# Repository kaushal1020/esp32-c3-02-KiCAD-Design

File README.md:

# ESP32-C3-02 KiCad Design

A custom **ESP32-C3-02 Development Board** designed from scratch using **KiCad**. This repository contains the complete hardware design, including schematic, PCB layout, and supporting files for manufacturing and development.

---

## 📖 Project Overview

This project demonstrates the complete design of an ESP32-C3-02 based development board. The board is intended for embedded systems, IoT applications, and custom hardware development.

The design was created entirely in KiCad, following standard PCB design practices.

---

## ✨ Features

- ESP32-C3-02 Wi-Fi + Bluetooth MCU
- USB programming interface
- Power regulation circuit
- Reset and Boot buttons
- GPIO breakout
- Status LEDs
- Compact PCB layout
- Designed completely in KiCad

---

## 📂 Repository Contents

- Schematic (.kicad_sch)
- PCB Layout (.kicad_pcb)
- KiCad Project Files
- Symbol Libraries
- Footprint Libraries
- Manufacturing Files (Gerbers)
- Bill of Materials (BOM)

---

## 🛠 Software Used

- KiCad 9
- ESP32-C3-02

## 🚀 Applications

- IoT Devices
- Embedded Systems
- Wireless Sensor Networks
- Industrial Monitoring
- Robotics

---

## 📋 Future Improvements

- Add USB-C interface
- Battery charging circuit
- On-board sensors
- Power optimization
- Improved GPIO labeling

---

## 📄 License

This project is intended for educational and learning purposes.

---

## 👨‍💻 Author

**Kaushal Kumar**

GitHub: https://github.com/kaushal1020

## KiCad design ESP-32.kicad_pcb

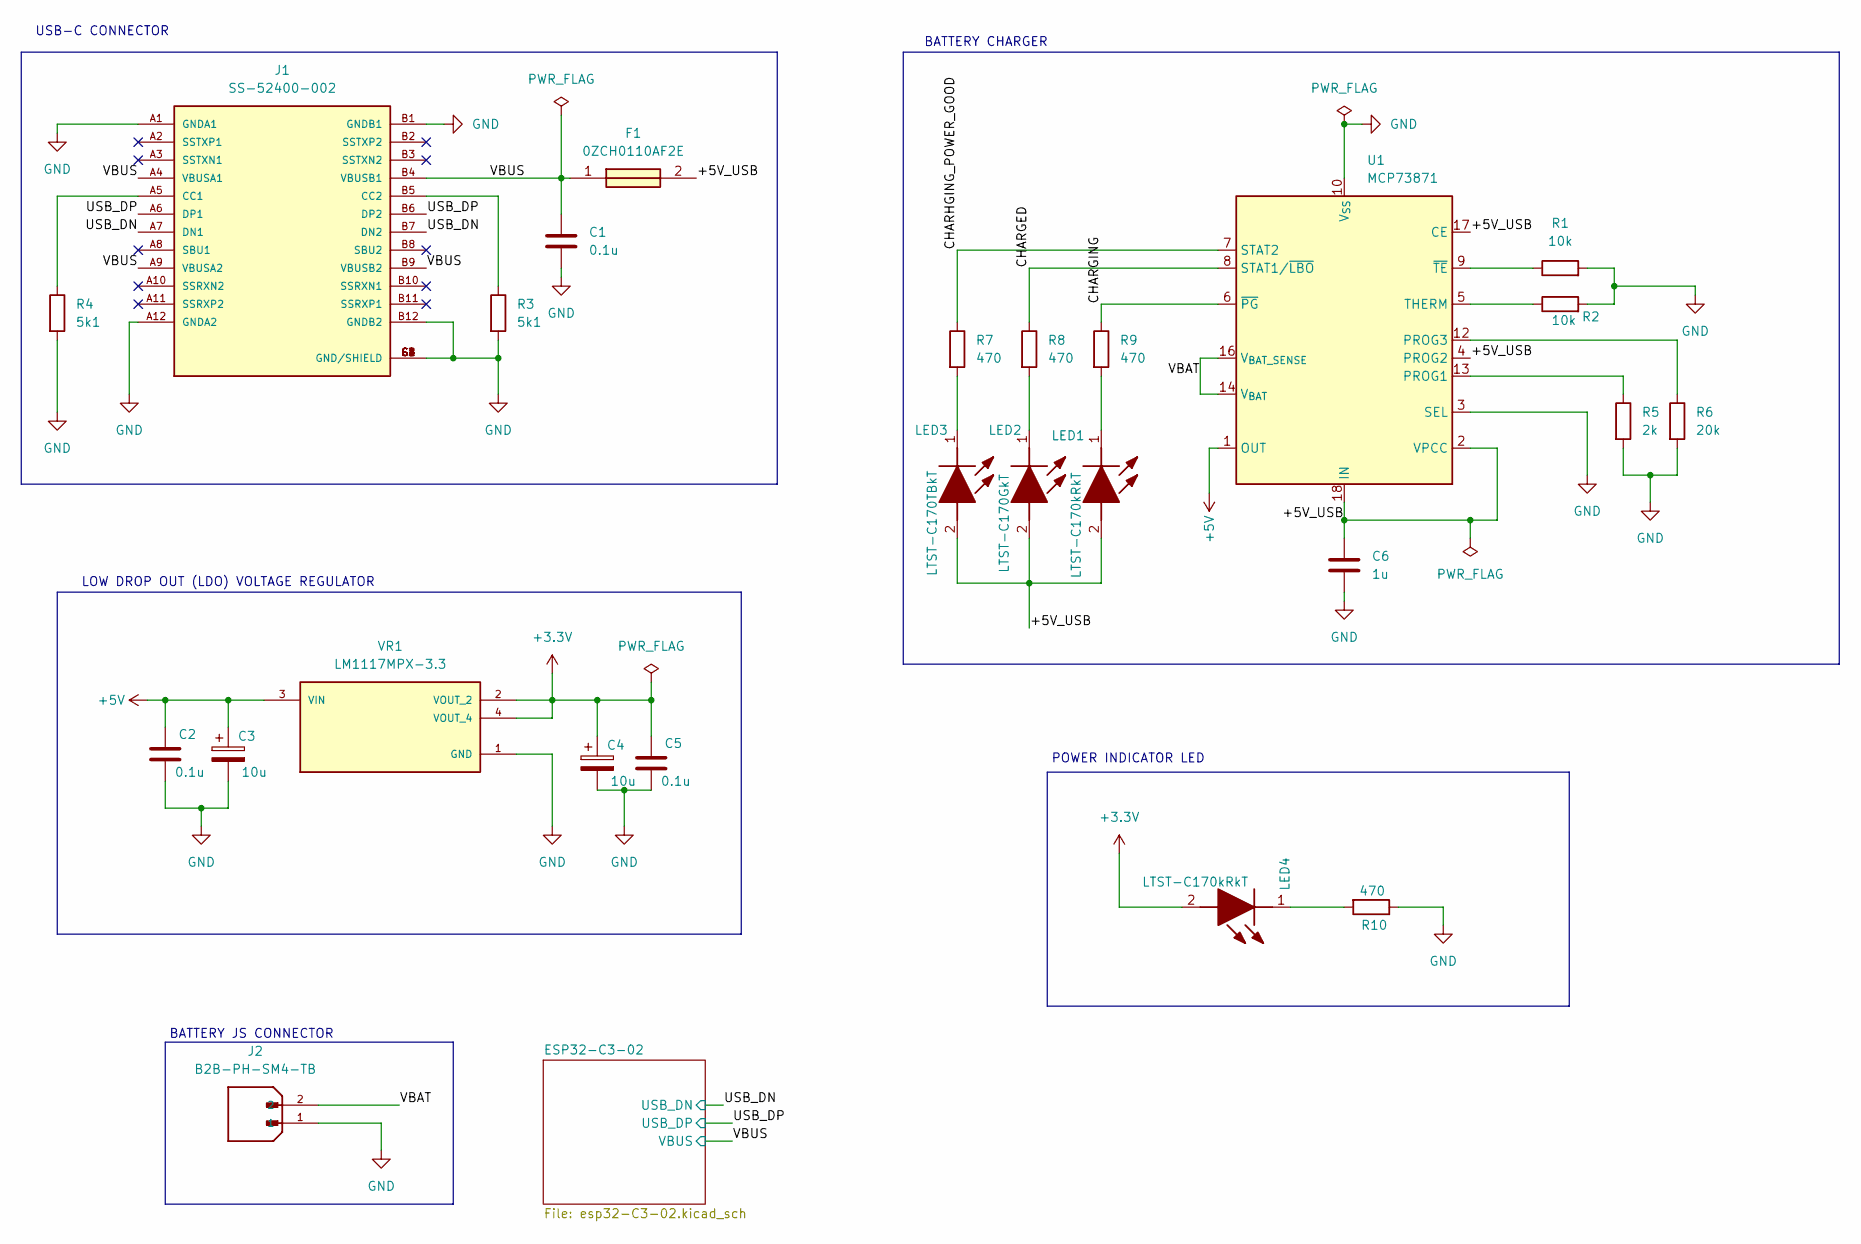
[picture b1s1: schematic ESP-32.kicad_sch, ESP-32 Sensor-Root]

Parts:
C1, C2, C5: 0.1u; C_0805_2012Metric
C3, C4: 10u; T491A
C6: 1u; C_0805_2012Metric
F1: 0ZCH0110AF2E; FUSC3226X100N; Manufacturer_Part_Number 0ZCH0110AF2E
J1: SS-52400-002; BELFUSE_SS-52400-002; PARTREV A0
J2: B2B-PH-SM4-TB; JST_B2B-PH-SM4-TB; PARTREV N/A
LED1, LED4: LTST-C170kRkT; LEDC2012X120N; Manufacturer_Part_Number LTST-C170KRKT; Mouser Part Number 859-LTST-C170KRKT
LED2: LTST-C170GkT; LEDC2012X120N; Manufacturer_Part_Number LTST-C170GKT; Mouser Part Number 859-LTST-C170GKT
LED3: LTST-C170TBkT; LEDC2012X120N; Manufacturer_Part_Number LTST-C170TBKT; Mouser Part Number 859-LTST-C170TBKT
R1, R2: 10k; R_0805_2012Metric
R3, R4: 5k1; R_0805_2012Metric
R5: 2k; R_0805_2012Metric
R6: 20k; R_0805_2012Metric
R7, R8, R9, R10: 470; R_0805_2012Metric
U1: MCP73871; QFN-20-1EP_4x4mm_P0.5mm_EP2.5x2.5mm
VR1: LM1117MPX-3.3; VREG_LM1117MPX-3.3

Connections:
+5V: C2.1, C3.1, U1.1 (OUT), U1.20 (OUT), VR1.3 (VIN)
/+5V_USB: C6.1, F1.2, LED1.2 (A), LED2.2 (A), LED3.2 (A), U1.2 (VPCC), U1.4 (PROG2), U1.17 (CE), U1.18 (IN), U1.19 (IN)
/CHARGED: R8.1, U1.8 (STAT1/~LBO)
/CHARGING: R9.1, U1.6 (~PG)
/CHARHGING_POWER_GOOD: R7.1, U1.7 (STAT2)
/USB_DN: J1.A7 (DN1), J1.B7 (DN2); also elsewhere on the board
/USB_DP: J1.A6 (DP1), J1.B6 (DP2); also elsewhere on the board
/VBAT: J2.2, U1.14 (V_{BAT}), U1.15 (V_{BAT}), U1.16 (V_{BAT_SENSE})
/VBUS: C1.1, F1.1, J1.A4 (VBUSA1), J1.A9 (VBUSA2), J1.B4 (VBUSB1), J1.B9 (VBUSB2); also elsewhere on the board
unnamed: J1.A5 (CC1), R4.1
unnamed: J1.B5 (CC2), R3.1
unnamed: LED1.1 (K), R9.2
unnamed: LED2.1 (K), R8.2
unnamed: LED3.1 (K), R7.2
unnamed: LED4.1 (K), R10.2
unnamed: R5.1, U1.13 (PROG1)
unnamed: R6.1, U1.12 (PROG3)
unnamed: R2.1, U1.5 (THERM)
unnamed: R1.1, U1.9 (~TE)

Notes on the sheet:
USB-C CONNECTOR
LOW DROP OUT (LDO) VOLTAGE REGULATOR
POWER INDICATOR LED
BATTERY JS CONNECTOR
BATTERY CHARGER

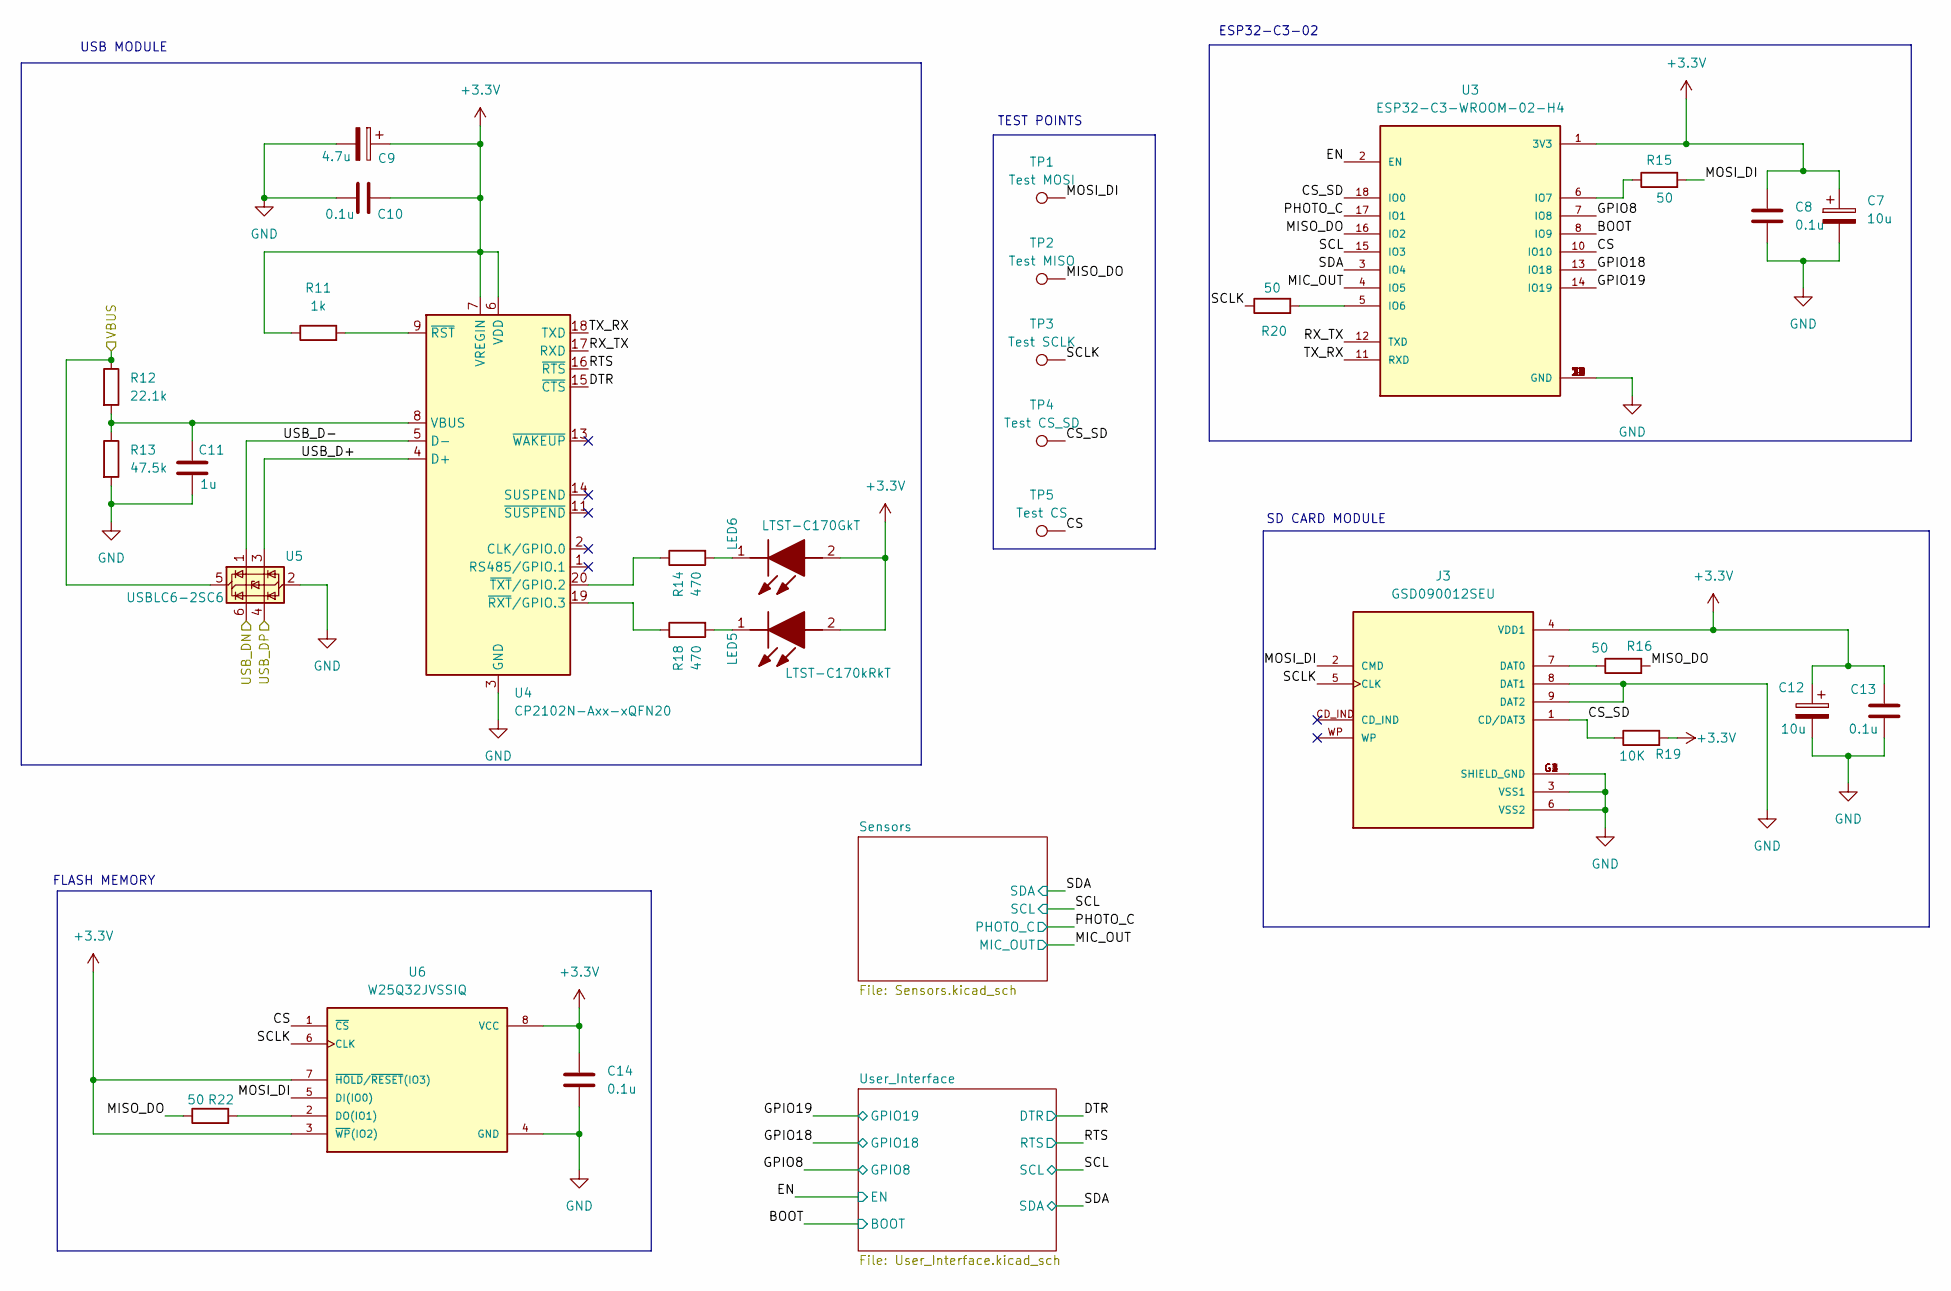
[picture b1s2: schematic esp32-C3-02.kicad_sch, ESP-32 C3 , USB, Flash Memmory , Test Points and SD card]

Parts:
C7, C12: 10u; T491A
C8, C10, C13, C14: 0.1u; C_0805_2012Metric
C9: 4.7u; T491A
C11: 1u; C_0805_2012Metric
J3: GSD090012SEU; AMPHENOL_GSD090012SEU; PARTREV E
LED5: LTST-C170kRkT; LEDC2012X120N; Manufacturer_Part_Number LTST-C170KRKT; Mouser Part Number 859-LTST-C170KRKT
LED6: LTST-C170GkT; LEDC2012X120N; Manufacturer_Part_Number LTST-C170GKT; Mouser Part Number 859-LTST-C170GKT
R11: 1k; R_0805_2012Metric
R12: 22.1k; R_0805_2012Metric
R13: 47.5k; R_0805_2012Metric
R14, R18: 470; R_0805_2012Metric
R15, R16, R20, R22: 50; R_0805_2012Metric
R19: 10K; R_0805_2012Metric
TP1: Test MOSI; TestPoint_Pad_D1.0mm
TP2: Test MISO; TestPoint_Pad_D1.0mm
TP3: Test SCLK; TestPoint_Pad_D1.0mm
TP4: Test CS_SD; TestPoint_Pad_D1.0mm
TP5: Test CS; TestPoint_Pad_D1.0mm
U3: ESP32-C3-WROOM-02-H4; MODULE_ESP32-C3-WROOM-02-H4
U4: CP2102N-Axx-xQFN20; SiliconLabs_QFN-20-1EP_3x3mm_P0.5mm_EP1.8x1.8mm
U5: USBLC6-2SC6; SOT-23-6
U6: W25Q32JVSSIQ; SOIC127P790X216-8N; M_PART_NUMBER W25QXX

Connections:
/ESP32-C3-02/BOOT: U3.8 (IO9); also elsewhere on the board
/ESP32-C3-02/CS: TP5.1 (1_1), U3.10 (IO10), U6.1 (~CS)
/ESP32-C3-02/CS_SD: J3.1 (CD/DAT3), R19.1, TP4.1 (1_1), U3.18 (IO0)
/ESP32-C3-02/DTR: U4.15 (~CTS); also elsewhere on the board
/ESP32-C3-02/EN: U3.2 (EN); also elsewhere on the board
/ESP32-C3-02/GPIO8: U3.7 (IO8); also elsewhere on the board
/ESP32-C3-02/GPIO18: U3.13 (IO18); also elsewhere on the board
/ESP32-C3-02/GPIO19: U3.14 (IO19); also elsewhere on the board
/ESP32-C3-02/MIC_OUT: U3.4 (IO5); also elsewhere on the board
/ESP32-C3-02/MISO_DO: R16.2, R22.1, TP2.1 (1_1), U3.16 (IO2)
/ESP32-C3-02/MOSI_DI: J3.2 (CMD), R15.2, TP1.1 (1_1), U6.5 (DI(IO0))
/ESP32-C3-02/PHOTO_C: U3.17 (IO1); also elsewhere on the board
/ESP32-C3-02/RTS: U4.16 (~RTS); also elsewhere on the board
/ESP32-C3-02/RX_TX: U3.12 (TXD), U4.17 (RXD)
/ESP32-C3-02/SCL: U3.15 (IO3); also elsewhere on the board
/ESP32-C3-02/SCLK: J3.5 (CLK), R20.1, TP3.1 (1_1), U6.6 (CLK)
/ESP32-C3-02/SDA: U3.3 (IO4); also elsewhere on the board
/ESP32-C3-02/TX_RX: U3.11 (RXD), U4.18 (TXD)
/ESP32-C3-02/USB_D+: U4.4 (D+), U5.3 (I/O2)
/ESP32-C3-02/USB_D-: U4.5 (D-), U5.1 (I/O1)
/USB_DN: U5.6 (I/O1); also elsewhere on the board
/USB_DP: U5.4 (I/O2); also elsewhere on the board
/VBUS: R12.1, U5.5 (VBUS); also elsewhere on the board
unnamed: J3.7 (DAT0), R16.1
unnamed: LED5.1 (K), R18.2
unnamed: LED6.1 (K), R14.2
unnamed: R20.2, U3.5 (IO6)
unnamed: R15.1, U3.6 (IO7)
unnamed: C11.1, R12.2, R13.1, U4.8 (VBUS)
unnamed: R11.2, U4.9 (~RST)
unnamed: R18.1, U4.19 (~RXT/GPIO.3)
unnamed: R14.1, U4.20 (~TXT/GPIO.2)
unnamed: R22.2, U6.2 (DO(IO1))

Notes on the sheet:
SD CARD MODULE
FLASH MEMORY
ESP32-C3-02
TEST POINTS
USB MODULE

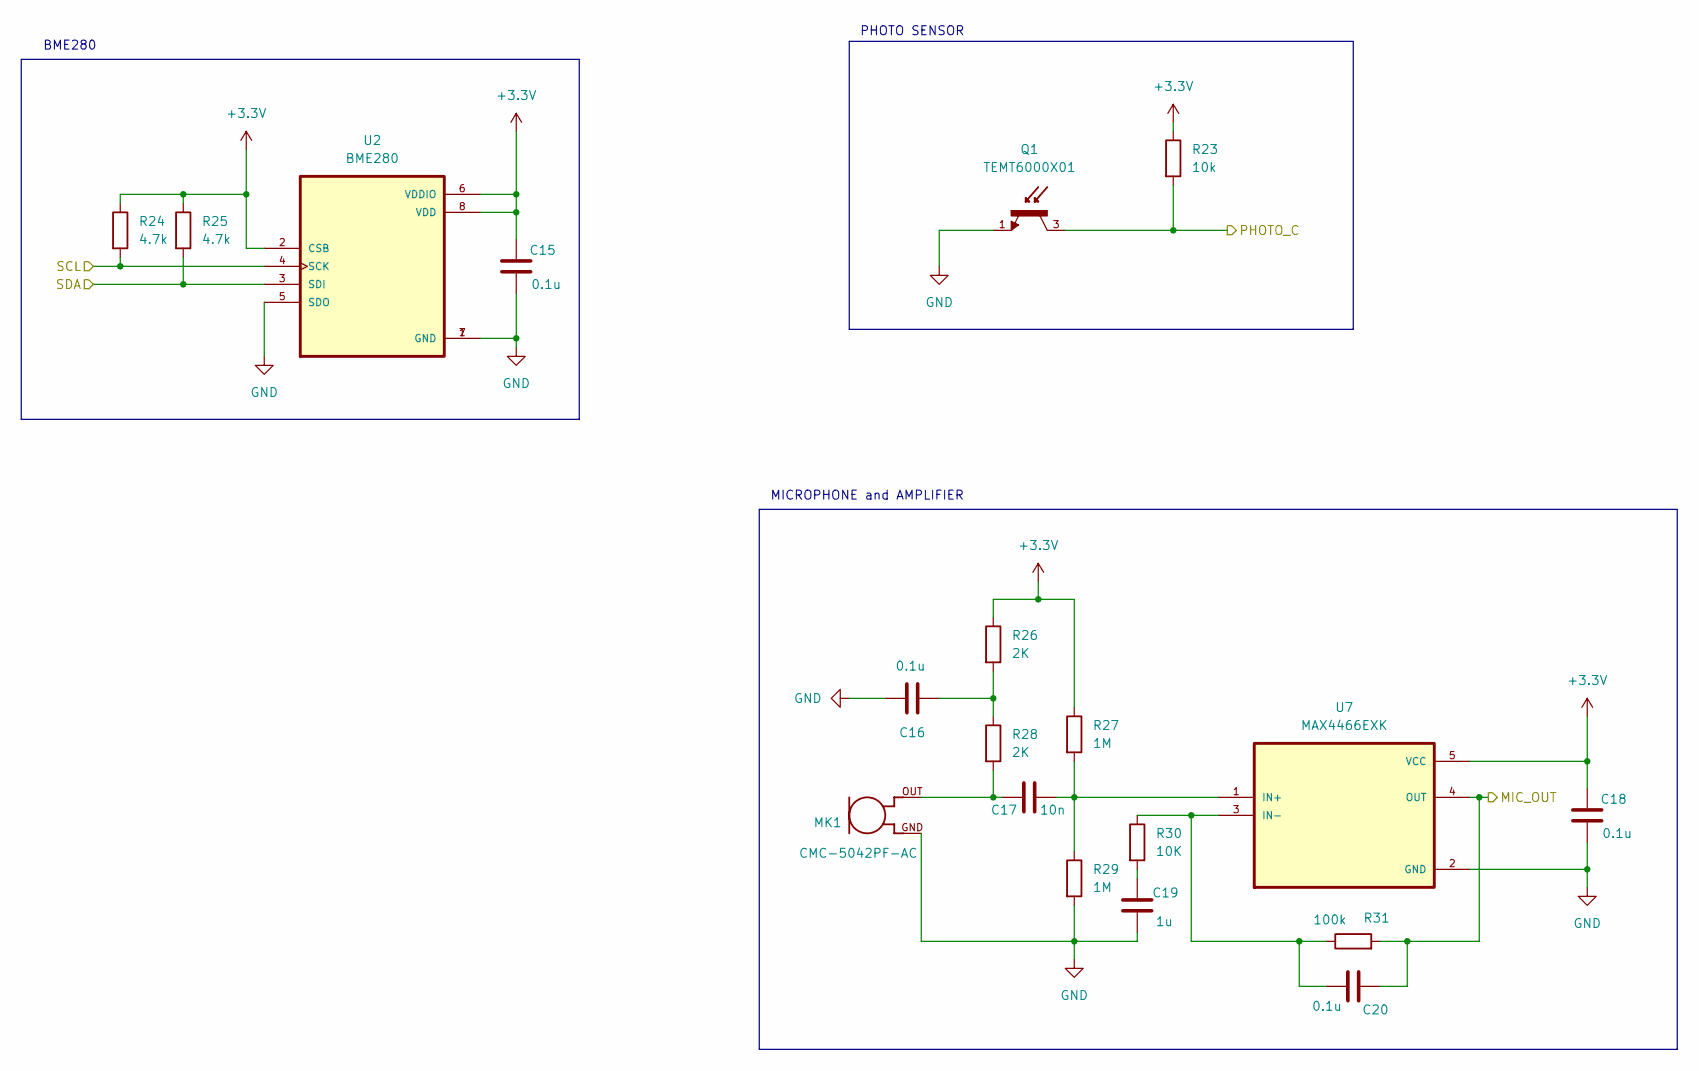
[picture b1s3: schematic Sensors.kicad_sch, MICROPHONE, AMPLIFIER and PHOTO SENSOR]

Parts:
C15, C16, C18, C20: 0.1u; C_0805_2012Metric
C17: 10n; C_0805_2012Metric
C19: 1u; C_0805_2012Metric
MK1: CMC-5042PF-AC; CUI_CMC-5042PF-AC
Q1: TEMT6000X01; TRANS_TEMT6000X01; PARTREV 1.9
R23: 10k; R_0805_2012Metric
R24, R25: 4.7k; R_0805_2012Metric
R26, R28: 2K; R_0805_2012Metric
R27, R29: 1M; R_0805_2012Metric
R30: 10K; R_0805_2012Metric
R31: 100k; R_0805_2012Metric
U2: BME280; PSON65P250X250X100-8N
U7: MAX4466EXK; SOT65P210X110-5N

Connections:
/ESP32-C3-02/MIC_OUT: C20.1, R31.2, U7.4 (OUT); also elsewhere on the board
/ESP32-C3-02/PHOTO_C: Q1.3, R23.2; also elsewhere on the board
/ESP32-C3-02/SCL: R24.2, U2.4 (SCK); also elsewhere on the board
/ESP32-C3-02/SDA: R25.2, U2.3 (SDI); also elsewhere on the board
unnamed: C16.1, R26.2, R28.1
unnamed: C17.1, MK1.OUT, R28.2
unnamed: C19.1, R30.2
unnamed: C17.2, R27.2, R29.1, U7.1 (IN+)
unnamed: C20.2, R30.1, R31.1, U7.3 (IN-)

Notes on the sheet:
PHOTO SENSOR
BME280
MICROPHONE and AMPLIFIER

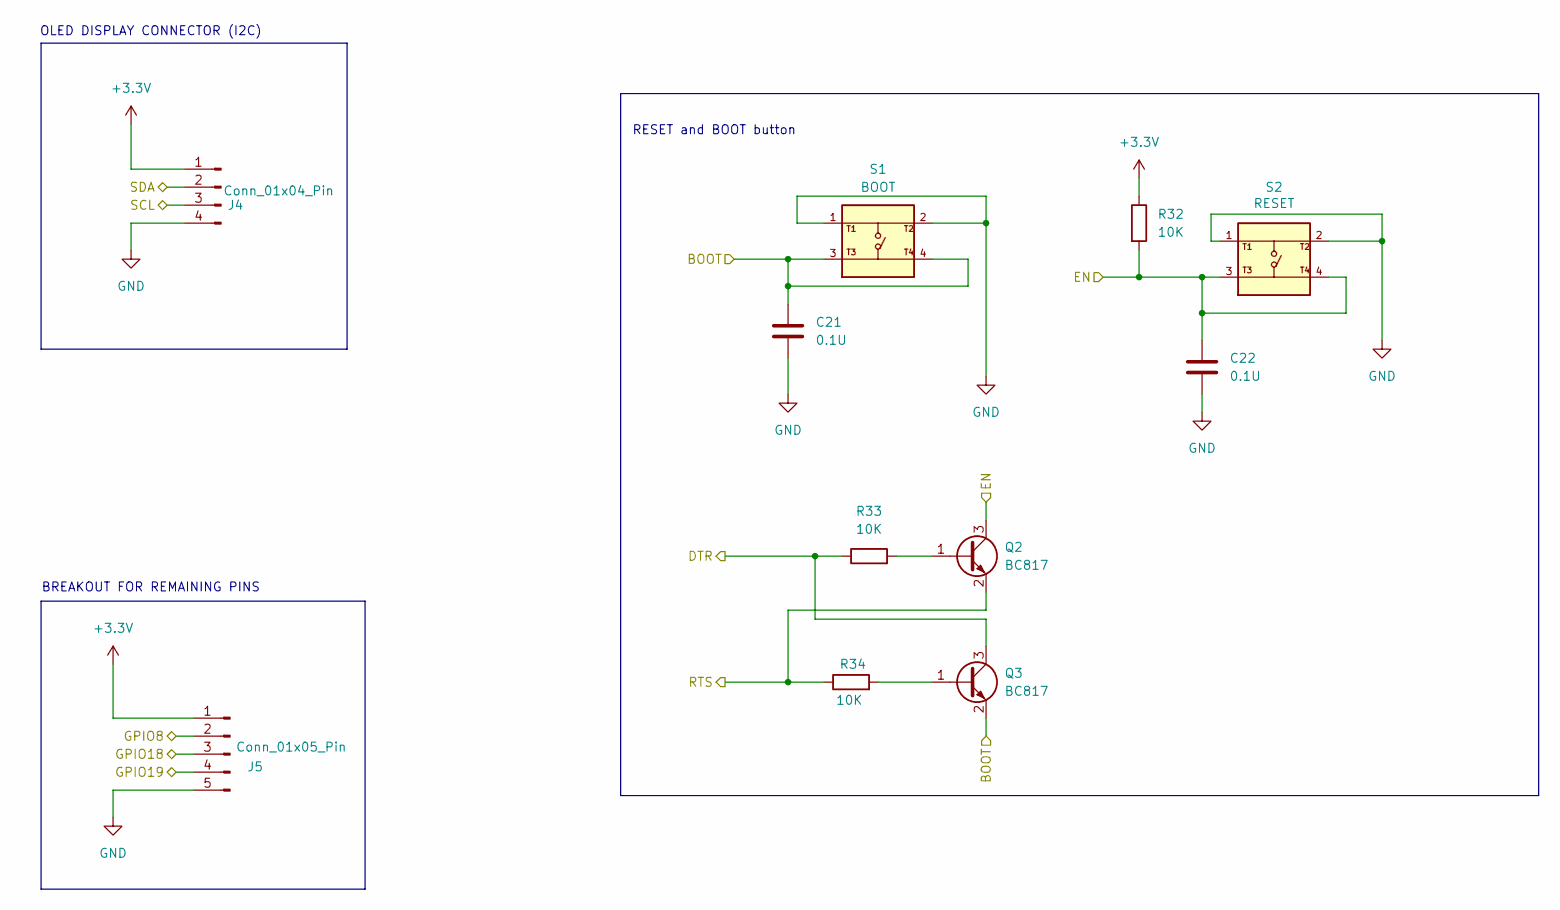
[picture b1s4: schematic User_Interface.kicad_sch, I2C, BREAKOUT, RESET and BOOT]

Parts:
C21, C22: 0.1U; C_0805_2012Metric
J4: Conn_01x04_Pin; PinHeader_1x04_P2.54mm_Vertical
J5: Conn_01x05_Pin; PinHeader_1x05_P2.54mm_Vertical
Q2, Q3: BC817; SOT-23
R32, R33, R34: 10K; R_0805_2012Metric
S1: BOOT; SW_USLPT2819DT2TR; PARTREV P
S2: RESET; SW_USLPT2819DT2TR; PARTREV P

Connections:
/ESP32-C3-02/BOOT: C21.1, Q3.2 (E), S1.3, S1.4; also elsewhere on the board
/ESP32-C3-02/DTR: Q3.3 (C), R33.1; also elsewhere on the board
/ESP32-C3-02/EN: C22.1, Q2.3 (C), R32.2, S2.3, S2.4; also elsewhere on the board
/ESP32-C3-02/GPIO8: J5.2; also elsewhere on the board
/ESP32-C3-02/GPIO18: J5.3; also elsewhere on the board
/ESP32-C3-02/GPIO19: J5.4; also elsewhere on the board
/ESP32-C3-02/RTS: Q2.2 (E), R34.1; also elsewhere on the board
/ESP32-C3-02/SCL: J4.3; also elsewhere on the board
/ESP32-C3-02/SDA: J4.2; also elsewhere on the board
unnamed: Q2.1 (B), R33.2
unnamed: Q3.1 (B), R34.2

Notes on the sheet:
BREAKOUT FOR REMAINING PINS
OLED DISPLAY CONNECTOR (I2C)
RESET and BOOT button

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
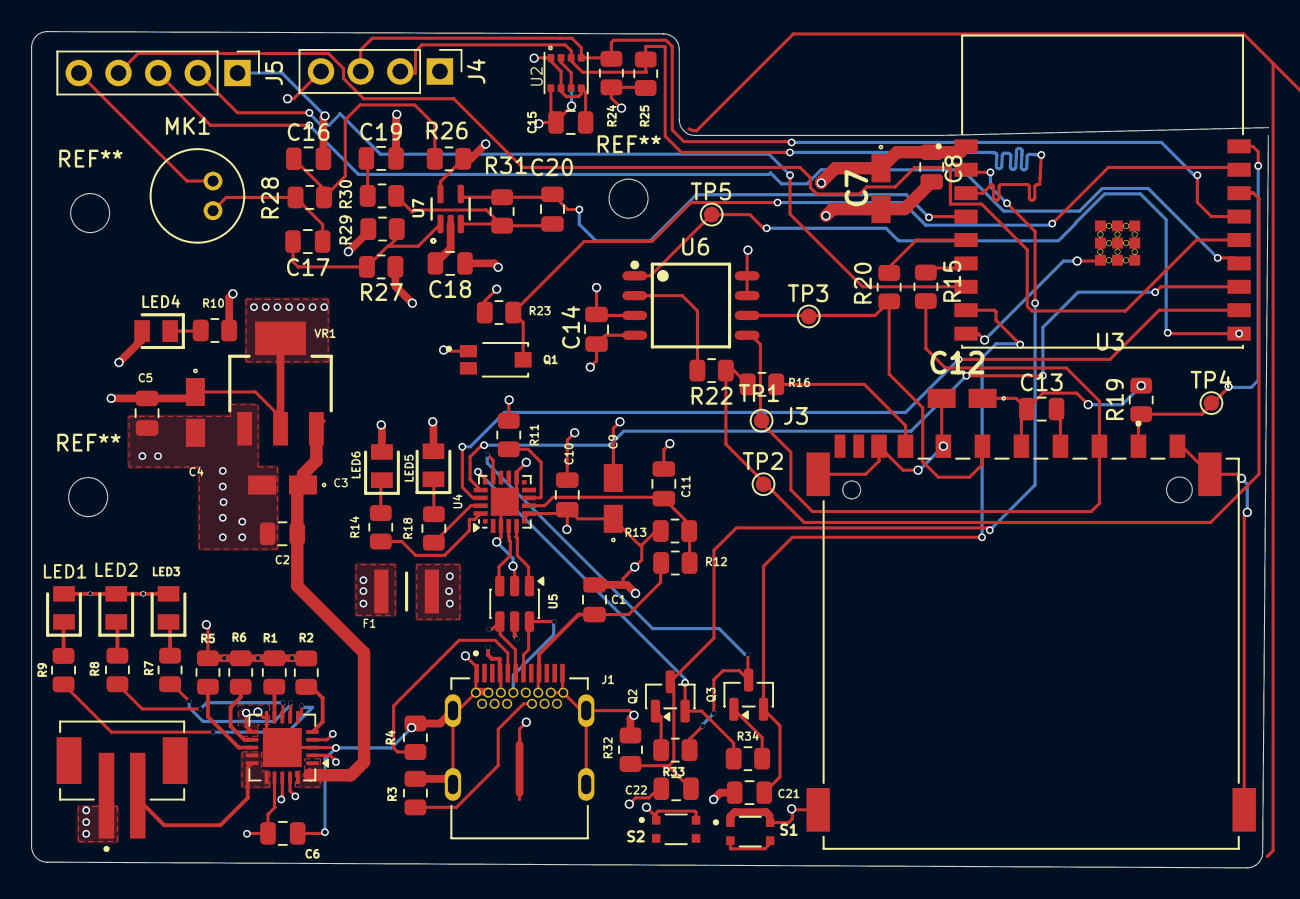
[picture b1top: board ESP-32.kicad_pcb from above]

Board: 4 copper layers, 79.2 x 53.6 mm, 85 parts (0 on the bottom side), 58 nets.
